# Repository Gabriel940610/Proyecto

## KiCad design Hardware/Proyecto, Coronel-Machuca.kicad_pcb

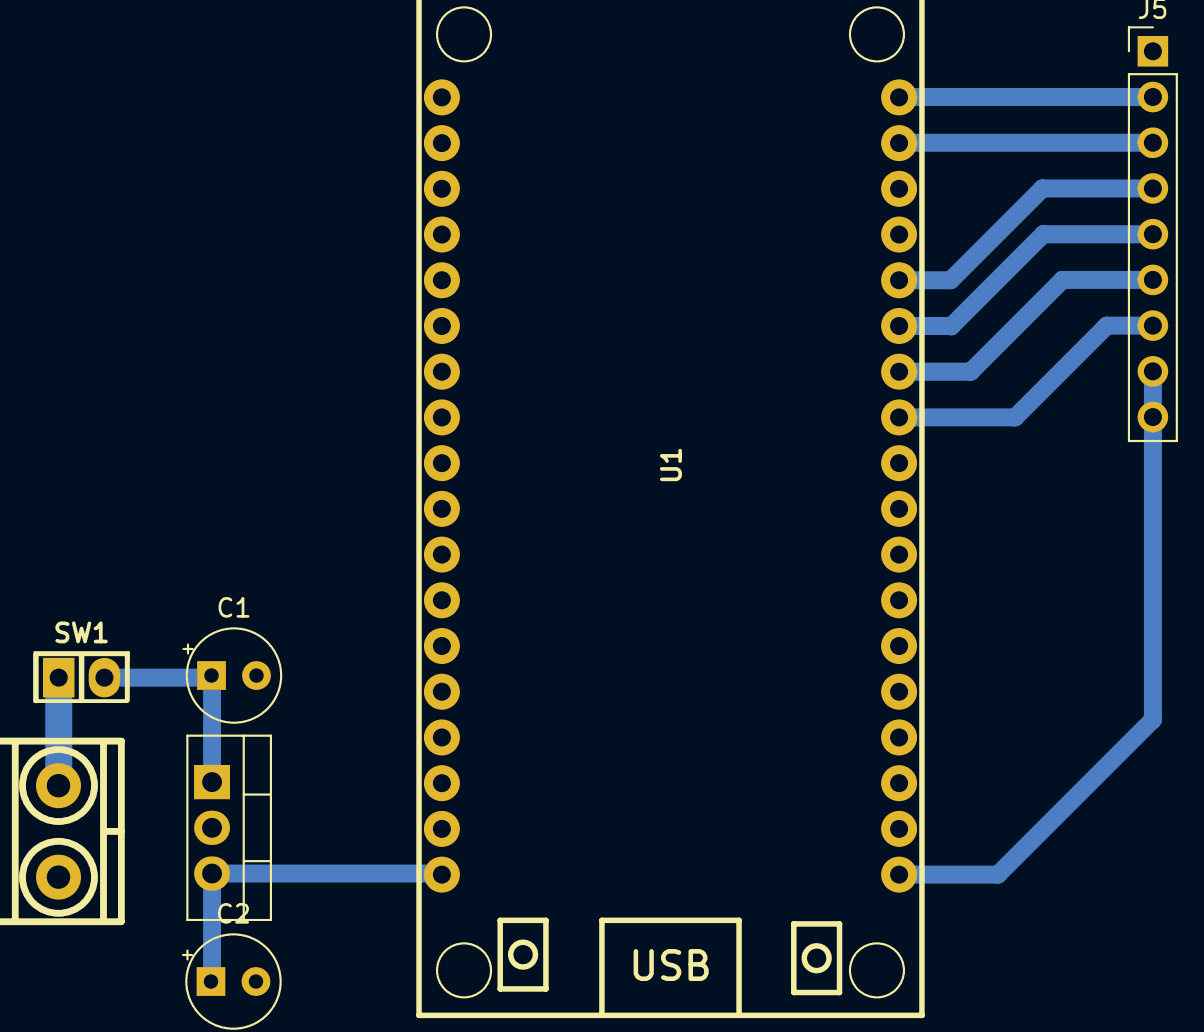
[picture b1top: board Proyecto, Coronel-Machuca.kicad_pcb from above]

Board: 2 copper layers, 7 parts (0 on the bottom side), 5 nets.

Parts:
C1, C2: C; CP_Radial_Tantal_D5.0mm_P2.50mm
J4: TB_1X2; BORNERA2_AZUL
J5: ILI9341; PinHeader_1x09_P2.54mm_Vertical
SW1: SW_Push; Pin_Header_2
U1: ESP32_DevKit_V1_DOIT; ESP32_DEVKIT_V1_DOIT
U2: L7805; TO-220-3_Vertical

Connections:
+3.3V: J5.8, J5.9, U1.19 (3V3)
GND: C1.2, C2.2, J4.1, J5.1, U2.2 (GND)
unnamed: C2.1, U1.18 (VIN), U2.3 (OUT)
unnamed: C1.1, SW1.2, U2.1 (IN)
VCC: J4.2, SW1.1

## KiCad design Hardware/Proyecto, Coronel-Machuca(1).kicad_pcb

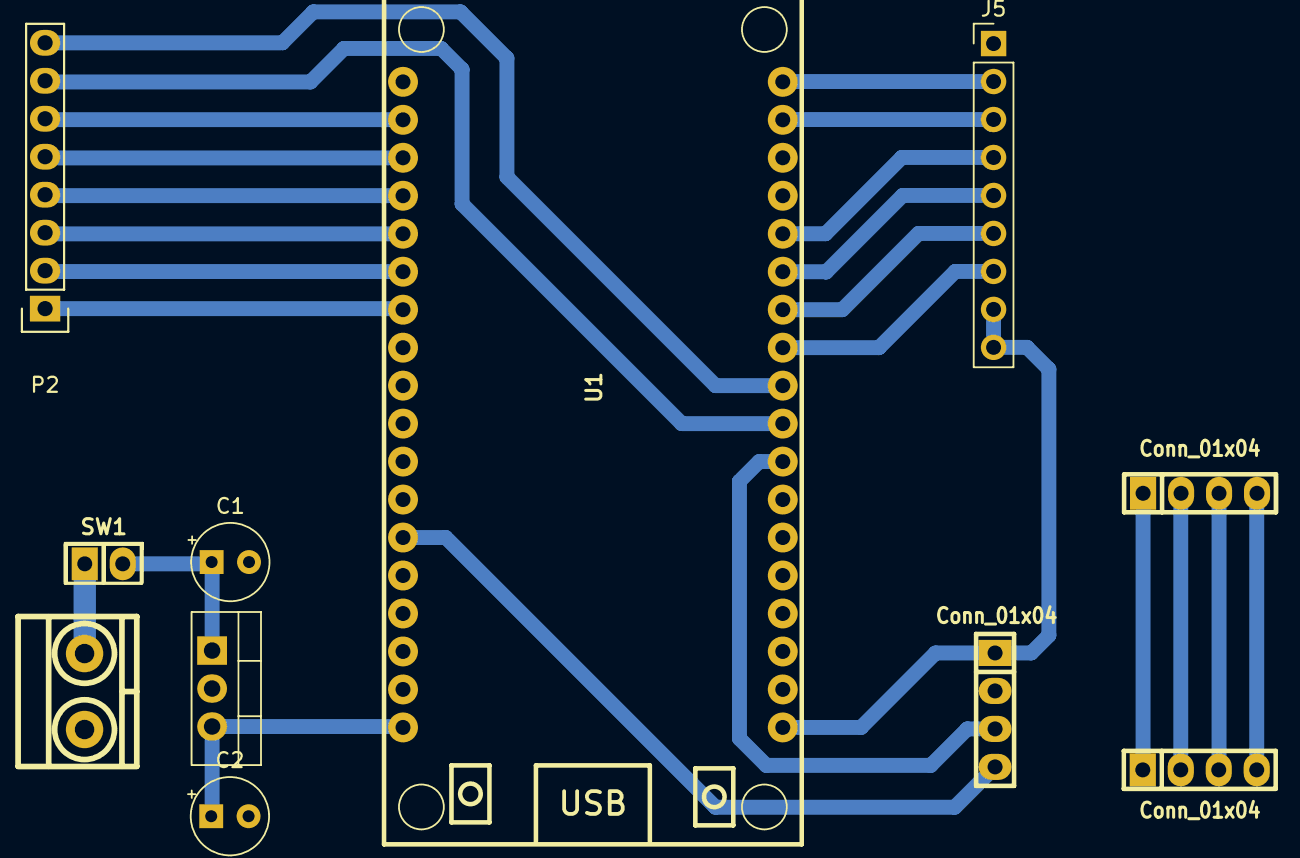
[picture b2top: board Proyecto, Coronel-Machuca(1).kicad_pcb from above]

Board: 2 copper layers, 11 parts (0 on the bottom side), 19 nets.

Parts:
C1, C2: C; CP_Radial_Tantal_D5.0mm_P2.50mm
J1, J2, J3: Conn_01x04; pin_strip_4
J4: TB_1X2; BORNERA2_AZUL
J5: ILI9341; PinHeader_1x09_P2.54mm_Vertical
P2: Tablero; Pin_Header_Straight_1x08
SW1: SW_Push; Pin_Header_2
U1: ESP32_DevKit_V1_DOIT; ESP32_DEVKIT_V1_DOIT
U2: L7805; TO-220-3_Vertical

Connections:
+3.3V: J3.1, J5.8, J5.9, U1.19 (3V3)
D1: P2.1, U1.7 (IO33)
D2: P2.2, U1.6 (IO32)
D3: P2.3, U1.5 (IO35)
D4: P2.4, U1.4 (IO34)
D5: P2.5, U1.3 (SENSOR_VN)
D6: P2.6, U1.2 (SENSOR_VP)
D7: P2.7, U1.27 (RX2)
D8: P2.8, U1.28 (TX2)
D(HX711): J3.3, U1.26 (IO4)
GND: C1.2, C2.2, J3.2, J4.1, J5.1, U2.2 (GND)
unnamed: J1.1, J2.1
unnamed: J1.2, J2.2
unnamed: J1.3, J2.3
unnamed: J1.4, J2.4
unnamed: C2.1, U1.18 (VIN), U2.3 (OUT)
unnamed: C1.1, SW1.2, U2.1 (IN)
SCK(HX711): J3.4, U1.13 (IO13)
VCC: J4.2, SW1.1

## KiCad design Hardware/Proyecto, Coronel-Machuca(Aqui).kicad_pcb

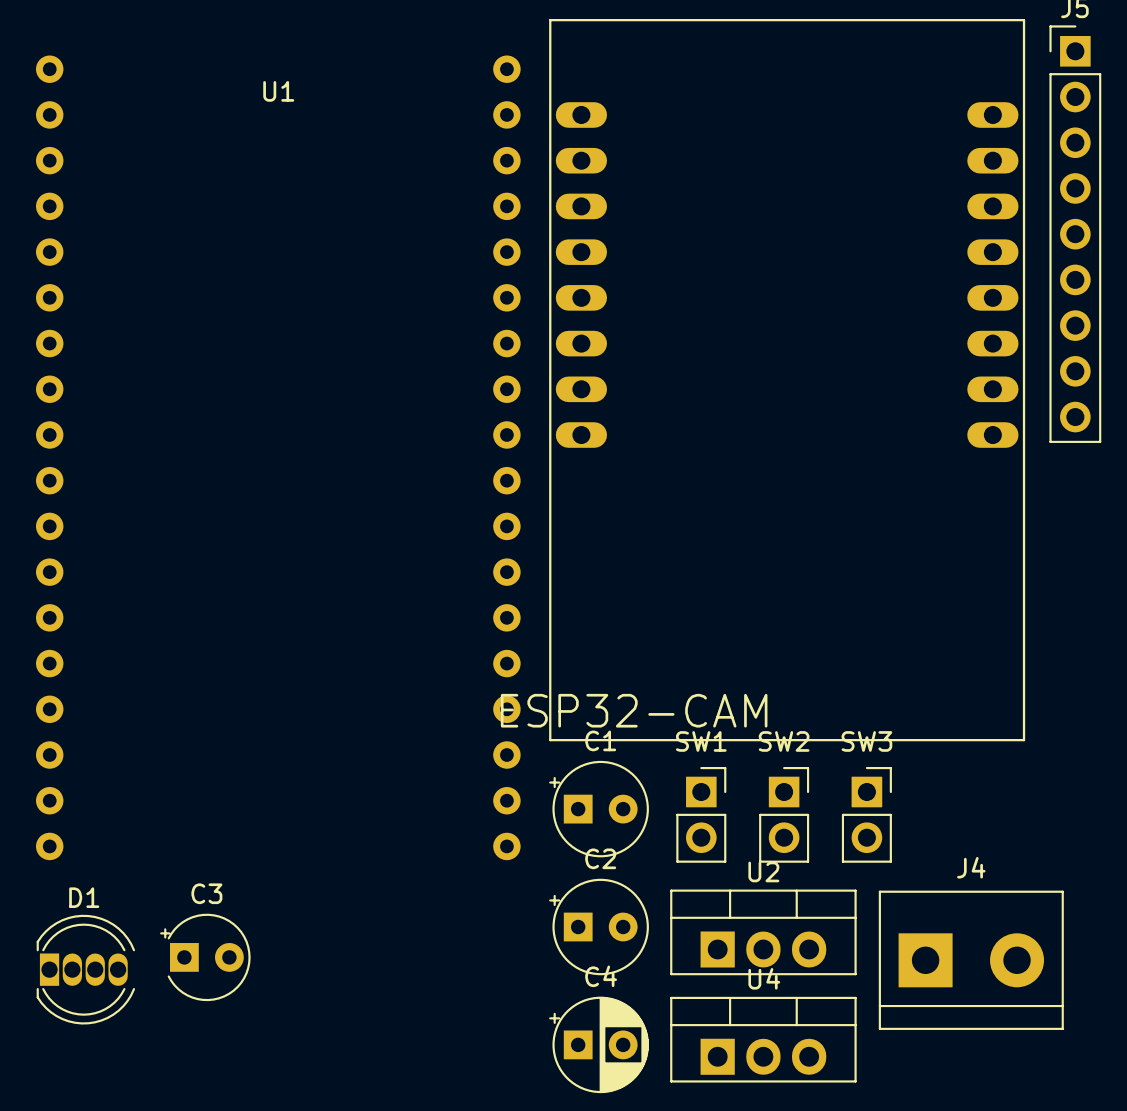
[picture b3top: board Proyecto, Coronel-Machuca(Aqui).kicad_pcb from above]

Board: 2 copper layers, 14 parts (0 on the bottom side), 12 nets, no tracks yet.

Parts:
C1, C2: C; CP_Radial_Tantal_D5.0mm_P2.50mm
C3: C; CP_Radial_Tantal_D4.5mm_P2.50mm
C4: C; CP_Radial_D5.0mm_P2.50mm
D1: APA-106-F5; LED_D5.0mm-4_RGB
J4: TB_1X2; TerminalBlock_bornier-2_P5.08mm
J5: ILI9341; PinHeader_1x09_P2.54mm_Vertical
SW1, SW2, SW3: SW_Push; PinSocket_1x02_P2.54mm_Vertical
U1: ESP32_DevKit_V1_DOIT; ESP32-DOIT-DEVKIT
U2, U4: L7805; TO-220-3_Vertical
U3: ESP32-CAM

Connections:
+3.3V: J5.8, J5.9, U1.19 (3V3)
GND: C1.2, C2.2, C3.2, C4.2, J4.1, J5.1, U2.2 (GND), U4.2 (GND)
unnamed: D1.4 (DI), U3.P$13 (GPIO15)
unnamed: D1.1 (DO), U3.P$11 (GPIO12)
unnamed: D1.2 (GND), SW3.2, U3.P$10 (GND@3)
unnamed: D1.3 (VDD), U3.P$14 (GPIO14)
unnamed: C2.1, U1.18 (VIN), U2.3 (OUT)
unnamed: C1.1, SW1.2, U2.1 (IN)
unnamed: C4.1, U3.P$9 (5V), U4.3 (OUT)
unnamed: SW3.1, U3.P$12 (GPIO13)
unnamed: C3.1, SW2.2, U4.1 (IN)
VCC: J4.2, SW1.1, SW2.1

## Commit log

2025-05-17 Create KiCad
2025-05-17 Create Code
2025-05-17 Create I
